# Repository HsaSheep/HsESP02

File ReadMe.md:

[schema](ESP-WROOM-02_BreakOut)

## About repo. ##

This repository converts "ESP-WROOM-02" module to 2.54 mm pitch.  
I am assuming to use on a solderless breadboard.

---
## Board's ##

#### V4 ####

Memo : V4はサンプル画像と作者の実物でいくつかの変更点が含まれていますが、回路な変更はありません。<br>
　　　　Sillk等にいくつかの軽微な修正が含まれています。また、それに伴いBuildDataが更新されています。

<table>
    <tr>
        <td>
            
        </td>
        <td>
            
        </td>
    </tr>
</table>

<!--
[schema]
-->

---

<details>
<summary>Old Version...</summary>

#### V3 ####

<table>
    <tr>
        <td>
            
        </td>
        <td>
            
        </td>
    </tr>
</table>

<!--
[schema]
-->

---

#### V2 ####

<table>
    <tr>
        <td>
            
        </td>
        <td>
            
        </td>
    </tr>
</table>

<!--
[schema]
-->

</details>

---

## This Repo... Empty??? ##
  
~~I am currently manufacturing the board.~~
~~All files are added as soon as normal operation can be confirmed.~~

~~(I am waiting for luggage from Elecrow.)~~

## 疲れたので日本語で追記します。 ##

Elecrowが中国の１０月の国のお休み的なやつ（国慶節）から帰ってきてくれたので
、頼んでいた基板が（かなり遅れて）到着し、現品を確認できました。

<table>
    <tr>
        <td>
            
        </td>
        <td>
            
        </td>
    </tr>
</table>

難しい部分を極力省いて、比較的小型で最小限の機能のブレークアウト基板を開発することが目的でしたので、
回路的に動作しない等のエラーはありませんでした。
そもそもAutoRoutingも使ってるので、失敗する要素が少ないんですが、やっぱり不安でして。

今回の目標であった、
* Reset、Boot0 および ユーザスイッチ1個を実装する。
* 全てハード的にプルアップする(マイコンでプルアップダウンをしない)。
* ブレッドボードに直接刺せる幅で、なおかつ左右に1列ずつ余るようにする。
* 組み込んだりする際の為に、SWや書き込み端子部分を切り離せるようにする。

今回の製作で目標はとりあえず達成できたと思われるので、
設計データ等をバックアップも兼ねてアップロードして置きます。

利用は自由ですし、改変も問題ないと思います。むしろ、自分も他人様のライブラリを引っ張ってきて作っている身です。

もし、Elecrow等にガーバーぶん投げるついでに、BreakOut基板も投げたいけど作るのだるいなーって感じだった時は、一応、このデータで作れているので一緒に出すと現時点では5枚600~700円程度で作れますので割と安価だと思います。

~~もっとよくできたのが転がってそうな気がしますが…~~

ガーバーデータはKiCadフォルダ内のG_Silks_v*.zipです。基本的に数字は製作した順ですので、複数ある場合は最新を見てもらえると良いかと。
いらなくなったら最新残して消します。

一方、プロジェクトファイル自体はそのまま更新しています。内部的にはzipを弾いてGit管理しているので…。

あ、あと、世間がWiFiのセキュリティで騒いでいますね。クラックとかなんとか…
FWのアップデートがあるようなので、組み立て後にアップデートして見るのも良いかと。

その際だけはWindowsマシンがあると楽かもしれません…(実体験)

##  ファイルについて ##

* KiCad
> Kicadフォルダ内にはKiCadにて設計した基板のデータ等が入っています。

* Arduino
> Arduinoフォルダ内には基板組み立て後にLED,およびWiFi,と適当なピン(デフォルトではbeep_pinとして5ピンを指定しています)をテストするためのスケッチです。ほとんどがESP8226のHttpServerのスケッチ例そのままですが、beep_pinの名の通り、圧電スピーカを接続し、状況を音で知らせたり、MACアドレス制限(を、していて不便だったので、制限)をしている場合のためにMACアドレスを表示するようになっています。SSIDとPassWordをそれぞれ自分のWiFiものに書き換えて制作したボードに書き込み、テストしてみてください。(APとして動作するように書き換えてもいいかもしれませんね。自分はネットに接続したまま使用したいのでこのような仕様となっています。)

<details>
<summary>スケッチの使い方...</summary>

>> OTA(Over The Air 無線LAN経由によるUpdate )を使用してみたい場合
>> 1. Boot0スイッチを使用して起動しシリアル接続にてHsESP02_BasicOTA.inoを書き込んでください。
>> 1. その後、スケッチを書き込みする際にはBasicOTAに追記する形で作成し、ArduinoIDE上のシリアルポートにてネットワークポートに表示されるOTA用ポートを指定して ***Boot0スイッチ等でブートモードに入ったりはせずに*** Uploadをしてください。
>> 1. (今後はHsESP02_BasicOTA.inoやその元になっているBasicOTA.ino等にアップデートがない限り、１を実行する必要はありません。)

>> OTAを使用しない場合
>> 1. Boot0スイッチを使用して起動しシリアル接続にてHsESP02_ESP-WROOM-02_Test.inoを書き込んで動作を確認します。

</details>

##### 念のため #####
何かあっても責任はとりません。
ご自身の判断のもと行ってください。

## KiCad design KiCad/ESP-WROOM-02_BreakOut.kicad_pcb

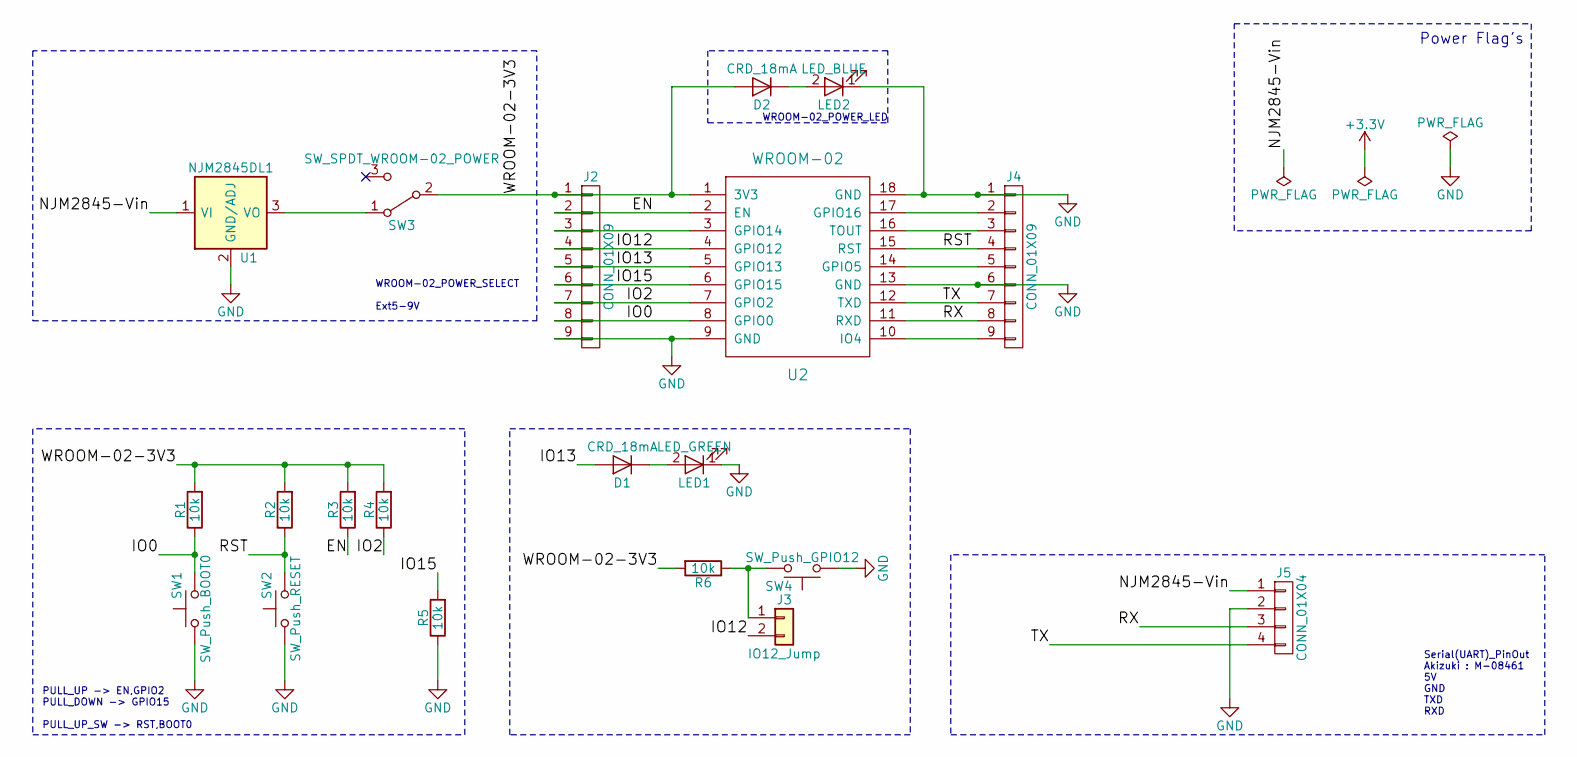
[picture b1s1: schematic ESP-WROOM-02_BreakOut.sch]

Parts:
D1, D2: CRD_18mA; D_1206
J2, J4: CONN_01X09; Pin_Header_Straight_1x09_Pitch2.54mm
J3: IO12_Jump; JUMPER-SOLDER-3mm
J5: CONN_01X04; Pin_Header_Straight_1x04_Pitch2.54mm
LED1: LED_GREEN; LED_0805
LED2: LED_BLUE; LED_0805
R1, R2, R3, R4, R5, R6: 10k; R_0603_HandSoldering
SW1: SW_Push_BOOT0; SW_DIP_x1_W7.62mm_Slide_MOD_TVBP06-B043C
SW2: SW_Push_RESET; SW_DIP_x1_W7.62mm_Slide_MOD_TVBP06-B043C
SW3: SW_SPDT_WROOM-02_POWER; Pin_Header_Straight_1x03_Pitch2.54mm
SW4: SW_Push_GPIO12; SW_DIP_x1_W7.62mm_Slide_MOD_TVBP06-B043C
U1: NJM2845DL1; NJM2845
U2: WROOM-02

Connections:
/EN: J2.2, R3.1, U2.2 (EN)
/IO0: J2.8, R1.1, SW1.2, U2.8 (GPIO0)
/IO2: J2.7, R4.1, U2.7 (GPIO2)
/IO12: J2.4, J3.2, U2.4 (GPIO12)
/IO13: D1.2 (A), J2.5, U2.5 (GPIO13)
/IO15: J2.6, R5.2, U2.6 (GPIO15)
/NJM2845-Vin: J5.1, U1.1 (VI)
/RST: J4.4, R2.1, SW2.2, U2.15 (RST)
/RX: J4.8, J5.3, U2.11 (RXD)
/TX: J4.7, J5.4, U2.12 (TXD)
/WROOM-02-3V3: D2.2 (A), J2.1, R1.2, R2.2, R3.2, R4.2, R6.2, SW3.2 (B), U2.1 (3V3)
GND: J2.9, J4.1, J4.6, J5.2, LED1.1 (K), LED2.1 (K), R5.1, SW1.1, SW2.1, SW4.1, U1.2 (GND/ADJ), U2.9 (GND), U2.13 (GND), U2.18 (GND)
unnamed: D1.1 (K), LED1.2 (A)
unnamed: D2.1 (K), LED2.2 (A)
unnamed: J2.3, U2.3 (GPIO14)
unnamed: J3.1, R6.1, SW4.2
unnamed: J4.2, U2.17 (GPIO16)
unnamed: J4.3, U2.16 (TOUT)
unnamed: J4.5, U2.14 (GPIO5)
unnamed: J4.9, U2.10 (IO4)
unnamed: SW3.1 (A), U1.3 (VO)

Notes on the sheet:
PULL_UP -> EN,GPIO2 PULL_DOWN -> GPIO15 PULL_UP_SW -> RST,BOOT0
Serial(UART)_PinOut Akizuki : M-08461 5V GND TXD RXD
WROOM-02_POWER_SELECT Ext5-9V
WROOM-02_POWER_LED
Power Flag's

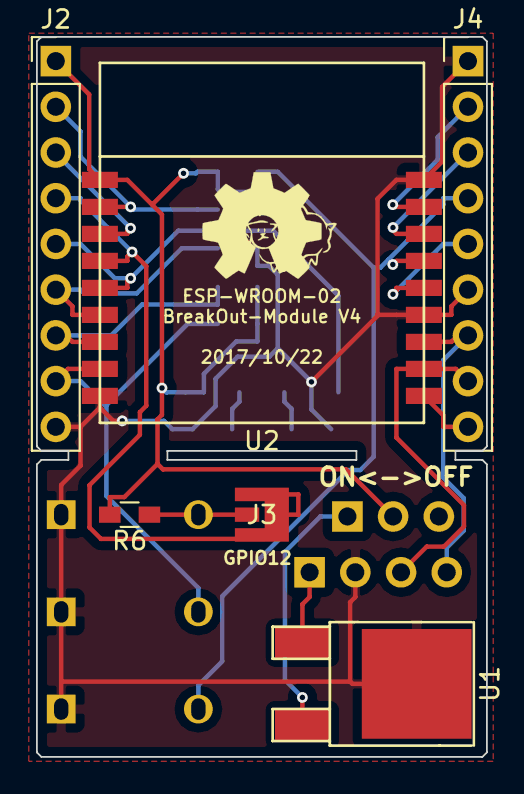
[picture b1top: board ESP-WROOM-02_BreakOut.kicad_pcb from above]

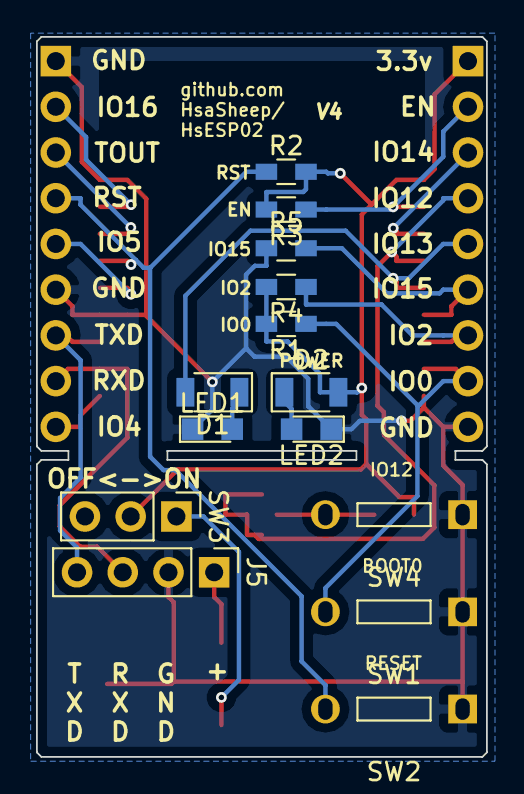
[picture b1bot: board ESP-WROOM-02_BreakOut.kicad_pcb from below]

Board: 2 copper layers, 25.0 x 40.0 mm, 20 parts (14 on the bottom side), 21 nets.

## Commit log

2017-09-01 Create ReadMe.md
    ...
2017-09-01 add Img
    add BreakOutModule Top and Bottom view.
2017-09-01 test readme.md
2017-09-04 ReadMe.md changed.
2017-09-12 add version3 image in /doc
2017-09-12 change v3 bottom image
2017-09-22 Update ReadMe.md
    huuu.
2017-09-22 Update ReadMe.md
    add space.
2017-09-22 Update ReadMe.md
    add '-'.
2017-10-21 Update Readme.md and add ./KiCaD , ./Arduino(Set SSID and PW)
2017-10-21 rename *.PNG -> *.png (怒
2017-10-21 doc/:変更
2017-10-21 画像サイズ調整
2017-10-21 画像サイズ調整2
2017-10-21 Readme.md 画像サイズ 今日のところは最終更新(予定)
2017-10-22 OTA用.ino追加とそれに伴うReadMe.mdの追記
2017-10-22 Serialをrootで表示する機能とかテスト用に実装
2017-10-23 テストプログラムアップデート
2017-10-23 とりあえず使えるものをコミット。Rootはシリアル受信したものをテキストとして素で吐き出します。
2017-10-23 WIFI_SETTING.hに両方とも統一
2017-10-23 WiFiの宣言周りの変更
2017-10-24 .ino内のincludeを変更
